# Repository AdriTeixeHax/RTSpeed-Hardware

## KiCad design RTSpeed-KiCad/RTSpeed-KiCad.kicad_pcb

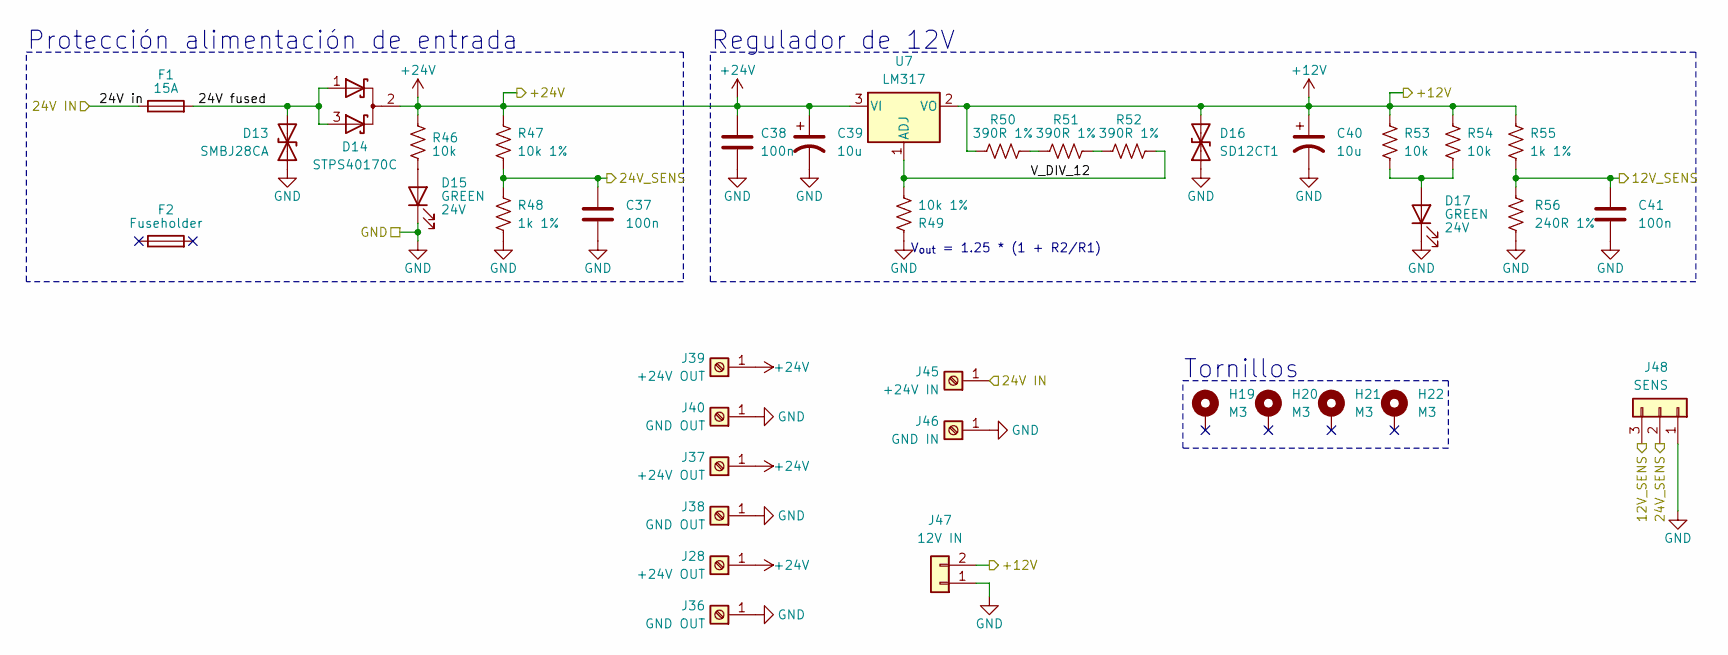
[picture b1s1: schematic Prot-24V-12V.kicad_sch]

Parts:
C37, C38, C41: 100n; C_0603_1608Metric; LCSC part C5137636
C39, C40: 10u; CP_Elec_4x5.4; LCSC part C72484
D13: SMBJ28CA; D_SMB; LCSC part C151259
D14: STPS40170C; TO-220-3_Vertical; LCSC part C222365
D15, D17: GREEN; LED_0805_2012Metric; LCSC part C965815
D16: SD12CT1; D_SOD-323_HandSoldering; LCSC part C328100
F1: 15A; Fuseholder_Automotive; LCSC part C151095
F2: Fuseholder; LCSC part C19727305
H19, H20, H21, H22: M3; MountingHole_3.2mm_M3
J28, J37, J39: +24V OUT; MountingHole_2.5mm_Pad_TopBottom
J36, J38, J40: GND OUT; MountingHole_2.5mm_Pad_TopBottom
J45: +24V IN; MountingHole_2.5mm_Pad_TopBottom
J46: GND IN; MountingHole_2.5mm_Pad_TopBottom
J47: 12V IN; JST_PH_B2B-PH-K_1x02_P2.00mm_Vertical
J48: SENS; JST_PH_B3B-PH-K_1x03_P2.00mm_Vertical
R46, R53, R54: 10k; R_0603_1608Metric; LCSC part C126901
R47, R49: 10k 1%; R_0603_1608Metric; LCSC part C126901
R48: 1k 1%; R_0603_1608Metric; LCSC part C103198
R50, R51, R52: 390R 1%; R_0603_1608Metric; LCSC part C3016257
R55: 1k 1%; R_0603_1608Metric; LCSC part C126901
R56: 240R 1%; R_0603_1608Metric; LCSC part C286579
U7: LM317; TO-220-3_Vertical; LCSC part C3014307

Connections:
+12V: C40.1, D16.2 (A2), J47.2, R50.1, R53.1, R54.1, R55.1, U7.2 (VO); also elsewhere on the board
+24V: C38.1, C39.1, D14.2 (K), J28.1, J37.1, J39.1, R46.1, R47.1, U7.3 (VI); also elsewhere on the board
/ADC/CH0: C37.1, J48.2, R47.2, R48.2; also elsewhere on the board
/ADC/CH1: C41.1, J48.3, R55.2, R56.1; also elsewhere on the board
/Protección 24V-12V/24V fused: D13.2 (A2), D14.1 (A), D14.3 (A), F1.2
/Protección 24V-12V/24V in: F1.1, J45.1; also elsewhere on the board
/Protección 24V-12V/V_DIV_12: R49.2, R52.2, U7.1 (ADJ)
GND: C37.2, C38.2, C39.2, C40.2, C41.2, D13.1 (A1), D15.1 (K), D16.1 (A1), D17.1 (K), J36.1, J38.1, J40.1, J46.1, J47.1, J48.1, R48.1, R49.1, R56.2; also elsewhere on the board
unnamed: D15.2 (A), R46.2
unnamed: D17.2 (A), R53.2, R54.2
unnamed: R50.2, R51.1
unnamed: R51.2, R52.1

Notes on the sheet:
Protección alimentación de entrada
V_{out} = 1.25 * (1 + R2/R1)
Regulador de 12V
Tornillos

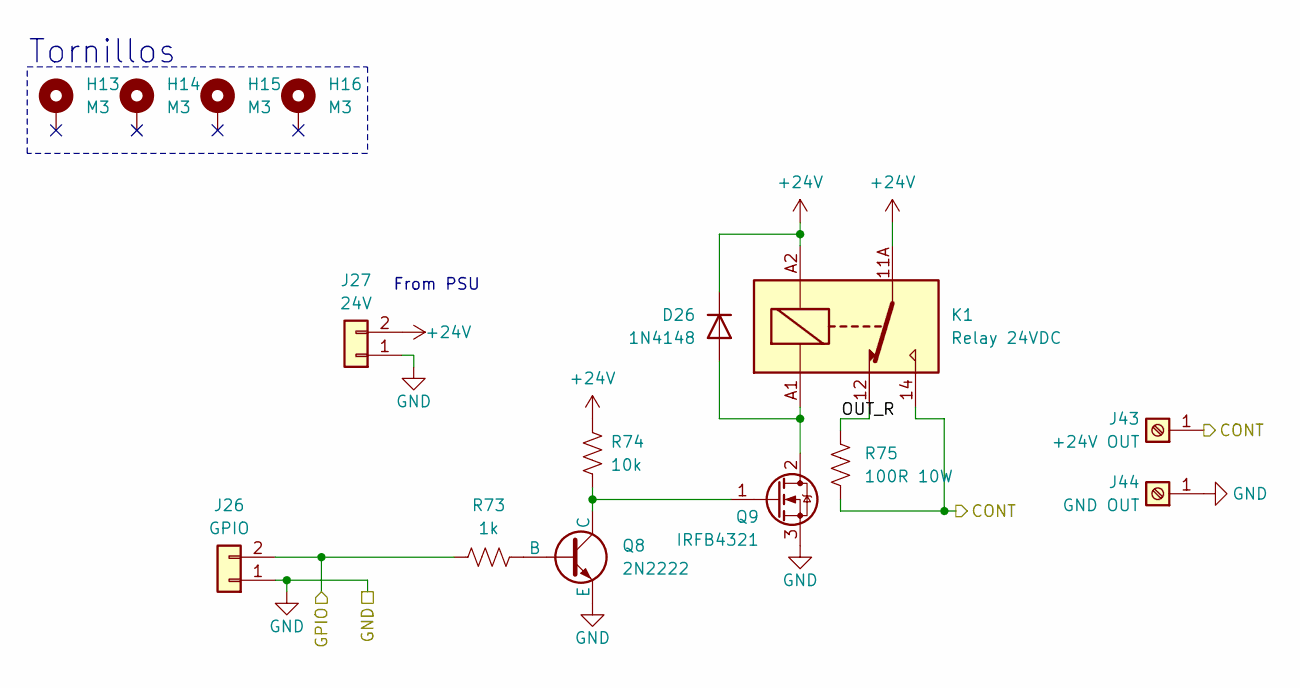
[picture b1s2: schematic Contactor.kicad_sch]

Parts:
D26: 1N4148; D_DO-35_SOD27_P7.62mm_Horizontal
H13, H14, H15, H16: M3; MountingHole_3.2mm_M3
J26: GPIO; JST_PH_B2B-PH-K_1x02_P2.00mm_Vertical
J27: 24V; Barrier_1x02
J43: +24V OUT; MountingHole_2.5mm_Pad_TopBottom
J44: GND OUT; MountingHole_2.5mm_Pad_TopBottom
K1: Relay 24VDC; Relay_SPDT_RAYEX-L90
Q8: 2N2222; TO-92_Inline
Q9: IRFB4321; TO-220-3_Vertical; LCSC part C2656
R73: 1k; R_Axial_DIN0207_L6.3mm_D2.5mm_P15.24mm_Horizontal
R74: 10k; R_Axial_DIN0207_L6.3mm_D2.5mm_P15.24mm_Horizontal
R75: 100R 10W; R_Power_22x9.5x9.5_P18mm

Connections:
+24V: D26.1 (K), J27.2, K1.11A, K1.11B, K1.A2, R74.1; also elsewhere on the board
/Contactor/OUT_R: K1.12, R75.1
/Microcontrolador/PA10: J26.2, R73.1; also elsewhere on the board
/Protección 24V-12V/24V in: J43.1, K1.14, R75.2; also elsewhere on the board
GND: J26.1, J27.1, J44.1, Q8.3 (E), Q9.3 (S); also elsewhere on the board
unnamed: D26.2 (A), K1.A1, Q9.2 (D)
unnamed: Q8.2 (B), R73.2
unnamed: Q8.1 (C), Q9.1 (G), R74.2

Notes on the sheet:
From PSU
Tornillos

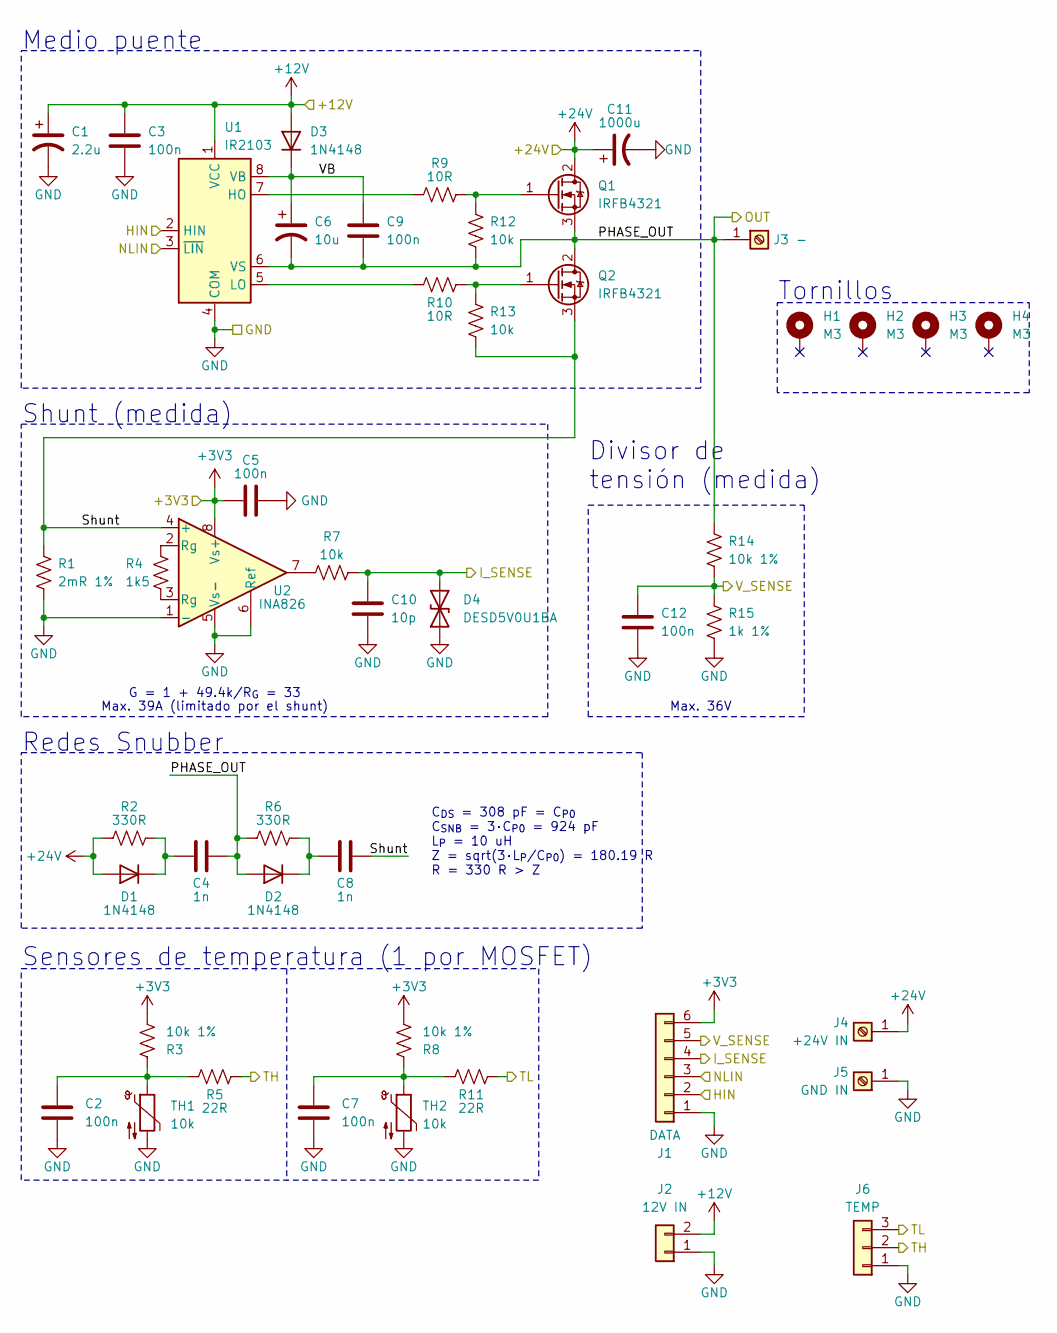
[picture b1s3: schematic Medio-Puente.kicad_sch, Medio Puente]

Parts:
C1: 2.2u; CP_Elec_4x5.4; LCSC part C72493
C2, C3, C5, C7, C9, C12: 100n; C_0603_1608Metric; LCSC part C5137636
C4, C8: 1n; C_0603_1608Metric; LCSC part C96090
C6: 10u; CP_Elec_4x5.4; LCSC part C72484
C10: 10p; C_0603_1608Metric; LCSC part C376764
C11: 1000u; CP_Radial_D12.5mm_P5.00mm; LCSC part C88743
D1, D2, D3: 1N4148; D_SOD-123; LCSC part C83528
D4: DESD5V0U1BA; D_SOD-323_HandSoldering; LCSC part C460442
H1, H2, H3, H4: M3; MountingHole_3.2mm_M3
J1: DATA; JST_PH_B6B-PH-K_1x06_P2.00mm_Vertical
J2: 12V IN; JST_PH_B2B-PH-K_1x02_P2.00mm_Vertical
J3: -; MountingHole_2.5mm_Pad_TopBottom
J4: +24V IN; MountingHole_2.5mm_Pad_TopBottom
J5: GND IN; MountingHole_2.5mm_Pad_TopBottom
J6: TEMP; JST_PH_B3B-PH-K_1x03_P2.00mm_Vertical
Q1, Q2: IRFB4321; TO-220-3_Vertical; LCSC part C2656
R1: 2mR 1%; R_2512_6332Metric; LCSC part C2994640
R2, R6: 330R; R_0603_1608Metric; LCSC part C2933198
R3, R8, R14: 10k 1%; R_0603_1608Metric; LCSC part C126901
R4: 1k5; R_0603_1608Metric; LCSC part C3016293
R5, R11: 22R; R_0603_1608Metric; LCSC part C163887
R7, R12, R13: 10k; R_0603_1608Metric; LCSC part C126901
R9, R10: 10R; R_0805_2012Metric; LCSC part C3016584
R15: 1k 1%; R_0603_1608Metric; LCSC part C103198
TH1: 10k; temp sensor; LCSC part C84036
TH2: 10k; temp sensor; LCSC part C123383
U1: IR2103; SOIC-8_3.9x4.9mm_P1.27mm; LCSC part C2957
U2: INA826; SOIC-8_3.9x4.9mm_P1.27mm; LCSC part C51631

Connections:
+3V3: C5.1, J1.6, R3.2, R8.2, U2.8 (Vs+); also elsewhere on the board
+12V: C1.1, C3.1, D3.2 (A), J2.2, U1.1 (VCC); also elsewhere on the board
+24V: C11.1, D1.2 (A), J4.1, Q1.2 (D), R2.2; also elsewhere on the board
/ADC/CH2: J6.2, R5.1; also elsewhere on the board
/ADC/CH3: J6.3, R11.1; also elsewhere on the board
/Medio-Puente-U/PHASE_OUT: C4.2, C6.2, C9.2, D2.2 (A), J3.1, Q1.3 (S), Q2.2 (D), R6.2, R12.1, R14.2, U1.6 (VS); also elsewhere on the board
/Medio-Puente-U/Shunt: C8.2, Q2.3 (S), R1.1, R13.1, U2.4 (+)
/Medio-Puente-U/VB: C6.1, C9.1, D3.1 (K), U1.8 (VB)
/Microcontrolador/PA8: J1.3, U1.3 (~LIN); also elsewhere on the board
/Microcontrolador/PA9: J1.2, U1.2 (HIN); also elsewhere on the board
/Microcontrolador/PB0: C12.1, J1.5, R14.1, R15.2; also elsewhere on the board
/Microcontrolador/PB1: C10.2, D4.2 (A2), J1.4, R7.2; also elsewhere on the board
GND: C1.2, C2.2, C3.2, C5.2, C7.2, C10.1, C11.2, C12.2, D4.1 (A1), J1.1, J2.1, J5.1, J6.1, R1.2, R15.1, TH1.2, TH2.2, U1.4 (COM), U2.1 (-), U2.5 (Vs-), U2.6 (Ref); also elsewhere on the board
unnamed: C2.1, R3.1, R5.2, TH1.1
unnamed: C7.1, R8.1, R11.2, TH2.1
unnamed: C4.1, D1.1 (K), R2.1
unnamed: C8.1, D2.1 (K), R6.1
unnamed: Q1.1 (G), R9.2, R12.2
unnamed: Q2.1 (G), R10.1, R13.2
unnamed: R4.1, U2.2 (Rg)
unnamed: R4.2, U2.3 (Rg)
unnamed: R7.1, U2.7
unnamed: R9.1, U1.7 (HO)
unnamed: R10.2, U1.5 (LO)

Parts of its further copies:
C13, C25: 2.2u; CP_Elec_4x5.4; LCSC part C72493
C14, C15, C17, C19, C21, C24, C26, C27, C29, C31, C33, C36: 100n; C_0603_1608Metric; LCSC part C5137636
C16, C20, C28, C32: 1n; C_0603_1608Metric; LCSC part C96090
C18, C30: 10u; CP_Elec_4x5.4; LCSC part C72484
C22, C34: 10p; C_0603_1608Metric; LCSC part C376764
C23, C35: 1000u; CP_Radial_D12.5mm_P5.00mm; LCSC part C88743
D5, D6, D7, D9, D10, D11: 1N4148; D_SOD-123; LCSC part C83528
D8, D12: DESD5V0U1BA; D_SOD-323_HandSoldering; LCSC part C460442
H5, H6, H7, H8, H9, H10, H11, H12: M3; MountingHole_3.2mm_M3
J7, J13: DATA; JST_PH_B6B-PH-K_1x06_P2.00mm_Vertical
J8, J14: 12V IN; JST_PH_B2B-PH-K_1x02_P2.00mm_Vertical
J9, J15: -; MountingHole_2.5mm_Pad_TopBottom
J10, J16: +24V IN; MountingHole_2.5mm_Pad_TopBottom
J11, J17: GND IN; MountingHole_2.5mm_Pad_TopBottom
J12, J18: TEMP; JST_PH_B3B-PH-K_1x03_P2.00mm_Vertical
Q3, Q4, Q5, Q6: IRFB4321; TO-220-3_Vertical; LCSC part C2656
R16, R31: 2mR 1%; R_2512_6332Metric; LCSC part C2994640
R17, R21, R32, R36: 330R; R_0603_1608Metric; LCSC part C2933198
R18, R23, R29, R33, R38, R44: 10k 1%; R_0603_1608Metric; LCSC part C126901
R19, R34: 1k5; R_0603_1608Metric; LCSC part C3016293
R20, R26, R35, R41: 22R; R_0603_1608Metric; LCSC part C163887
R22, R27, R28, R37, R42, R43: 10k; R_0603_1608Metric; LCSC part C126901
R24, R25, R39, R40: 10R; R_0805_2012Metric; LCSC part C3016584
R30, R45: 1k 1%; R_0603_1608Metric; LCSC part C103198
TH3, TH5: 10k; temp sensor; LCSC part C84036
TH4, TH6: 10k; temp sensor; LCSC part C123383
U3, U5: IR2103; SOIC-8_3.9x4.9mm_P1.27mm; LCSC part C2957
U4, U6: INA826; SOIC-8_3.9x4.9mm_P1.27mm; LCSC part C51631

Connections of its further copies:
+3V3: C17.1, C29.1, J7.6, J13.6, R18.2, R23.2, R33.2, R38.2, U4.8 (Vs+), U6.8 (Vs+); also elsewhere on the board
+12V: C13.1, C15.1, C25.1, C27.1, D7.2 (A), D11.2 (A), J8.2, J14.2, U3.1 (VCC), U5.1 (VCC); also elsewhere on the board
+24V: C23.1, C35.1, D5.2 (A), D9.2 (A), J10.1, J16.1, Q3.2 (D), Q5.2 (D), R17.2, R32.2; also elsewhere on the board
/ADC/CH4: J12.2, R20.1; also elsewhere on the board
/ADC/CH5: J12.3, R26.1; also elsewhere on the board
/ADC/CH6: J18.2, R35.1; also elsewhere on the board
/ADC/CH7: J18.3, R41.1; also elsewhere on the board
/Medio-Puente-V/PHASE_OUT: C16.2, C18.2, C21.2, D6.2 (A), J9.1, Q3.3 (S), Q4.2 (D), R21.2, R27.1, R29.2, U3.6 (VS); also elsewhere on the board
/Medio-Puente-V/Shunt: C20.2, Q4.3 (S), R16.1, R28.1, U4.4 (+)
/Medio-Puente-V/VB: C18.1, C21.1, D7.1 (K), U3.8 (VB)
/Medio-Puente-W/PHASE_OUT: C28.2, C30.2, C33.2, D10.2 (A), J15.1, Q5.3 (S), Q6.2 (D), R36.2, R42.1, R44.2, U5.6 (VS); also elsewhere on the board
/Medio-Puente-W/Shunt: C32.2, Q6.3 (S), R31.1, R43.1, U6.4 (+)
/Medio-Puente-W/VB: C30.1, C33.1, D11.1 (K), U5.8 (VB)
/Microcontrolador/PA0: C36.1, J13.5, R44.1, R45.2; also elsewhere on the board
/Microcontrolador/PA1: C34.2, D12.2 (A2), J13.4, R37.2; also elsewhere on the board
/Microcontrolador/PA2: J13.3, U5.3 (~LIN); also elsewhere on the board
/Microcontrolador/PA3: J13.2, U5.2 (HIN); also elsewhere on the board
/Microcontrolador/PA4: C24.1, J7.5, R29.1, R30.2; also elsewhere on the board
/Microcontrolador/PA5: C22.2, D8.2 (A2), J7.4, R22.2; also elsewhere on the board
/Microcontrolador/PA6: J7.3, U3.3 (~LIN); also elsewhere on the board
/Microcontrolador/PA7: J7.2, U3.2 (HIN); also elsewhere on the board
GND: C13.2, C14.2, C15.2, C17.2, C19.2, C22.1, C23.2, C24.2, C25.2, C26.2, C27.2, C29.2, C31.2, C34.1, C35.2, C36.2, D8.1 (A1), D12.1 (A1), J7.1, J8.1, J11.1, J12.1, J13.1, J14.1, J17.1, J18.1, R16.2, R30.1, R31.2, R45.1, TH3.2, TH4.2, TH5.2, TH6.2, U3.4 (COM), U4.1 (-), U4.5 (Vs-), U4.6 (Ref), U5.4 (COM), U6.1 (-), U6.5 (Vs-), U6.6 (Ref); also elsewhere on the board
unnamed: C14.1, R18.1, R20.2, TH3.1
unnamed: C19.1, R23.1, R26.2, TH4.1
unnamed: C26.1, R33.1, R35.2, TH5.1
unnamed: C31.1, R38.1, R41.2, TH6.1
unnamed: C16.1, D5.1 (K), R17.1
unnamed: C20.1, D6.1 (K), R21.1
unnamed: C28.1, D9.1 (K), R32.1
unnamed: C32.1, D10.1 (K), R36.1
unnamed: Q3.1 (G), R24.2, R27.2
unnamed: Q4.1 (G), R25.1, R28.2
unnamed: Q5.1 (G), R39.2, R42.2
unnamed: Q6.1 (G), R40.1, R43.2
unnamed: R19.1, U4.2 (Rg)
unnamed: R19.2, U4.3 (Rg)
unnamed: R22.1, U4.7
unnamed: R34.1, U6.2 (Rg)
unnamed: R34.2, U6.3 (Rg)
unnamed: R37.1, U6.7
unnamed: R24.1, U3.7 (HO)
unnamed: R25.2, U3.5 (LO)
unnamed: R39.1, U5.7 (HO)
unnamed: R40.2, U5.5 (LO)

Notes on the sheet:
Max. 39A (limitado por el shunt)
Medio puente
C_{DS} = 308 pF = C_{P0} C_{SNB} = 3·C_{P0} = 924 pF L_{P} = 10 uH Z = sqrt(3·L_{P}/C_{P0}) = 180.19 R R = 330 R > Z
Divisor de tensión (medida)
Max. 36V
Redes Snubber
Shunt (medida)
Tornillos
G = 1 + 49.4k/R_{G} = 33
Sensores de temperatura (1 por MOSFET)

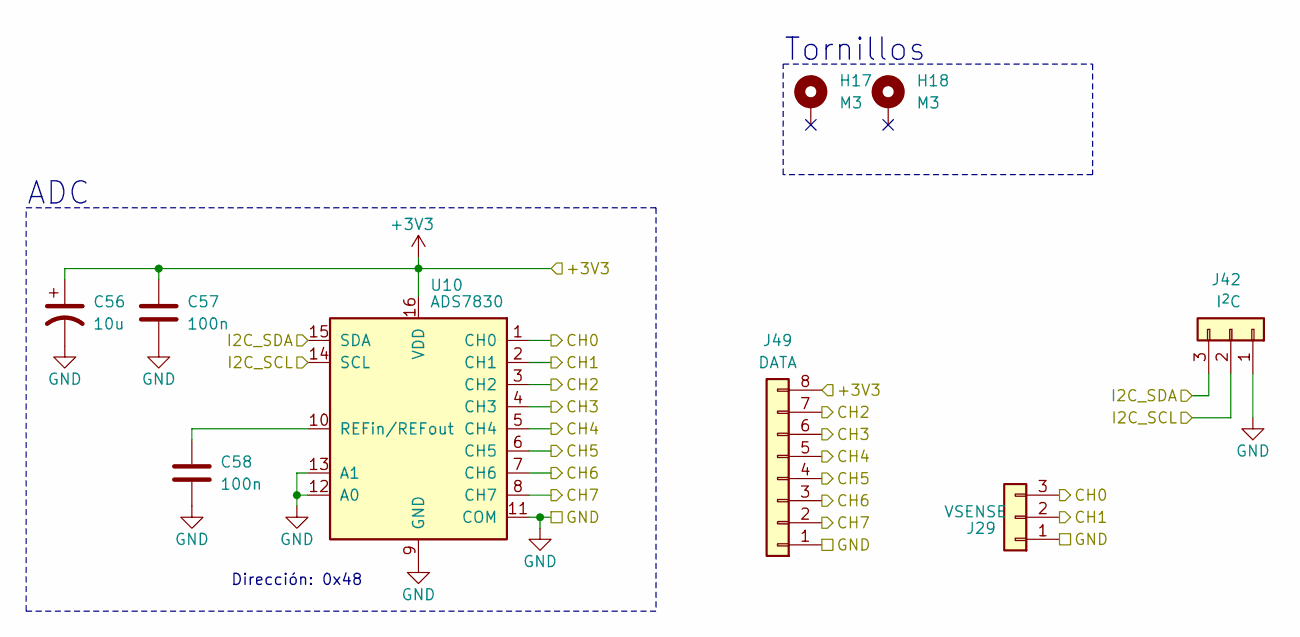
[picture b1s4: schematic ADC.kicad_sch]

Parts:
C56: 10u; CP_Elec_4x5.4; LCSC part C72484
C57, C58: 100n; C_0603_1608Metric; LCSC part C5137636
H17, H18: M3; MountingHole_3.2mm_M3
J29: VSENSE; JST_PH_B3B-PH-K_1x03_P2.00mm_Vertical
J42: I^{2}C; JST_PH_B3B-PH-K_1x03_P2.00mm_Vertical
J49: DATA; JST_PH_B8B-PH-K_1x08_P2.00mm_Vertical
U10: ADS7830; TSSOP-16_4.4x5mm_P0.65mm; LCSC part C161747

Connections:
+3V3: C56.1, C57.1, J49.8, U10.16 (VDD); also elsewhere on the board
/ADC/CH0: J29.3, U10.1 (CH0); also elsewhere on the board
/ADC/CH1: J29.2, U10.2 (CH1); also elsewhere on the board
/ADC/CH2: J49.7, U10.3 (CH2); also elsewhere on the board
/ADC/CH3: J49.6, U10.4 (CH3); also elsewhere on the board
/ADC/CH4: J49.5, U10.5 (CH4); also elsewhere on the board
/ADC/CH5: J49.4, U10.6 (CH5); also elsewhere on the board
/ADC/CH6: J49.3, U10.7 (CH6); also elsewhere on the board
/ADC/CH7: J49.2, U10.8 (CH7); also elsewhere on the board
/Microcontrolador/I2C_SCL: J42.2, U10.14 (SCL); also elsewhere on the board
/Microcontrolador/I2C_SDA: J42.3, U10.15 (SDA); also elsewhere on the board
GND: C56.2, C57.2, C58.2, J29.1, J42.1, J49.1, U10.9 (GND), U10.11 (COM), U10.12 (A0), U10.13 (A1); also elsewhere on the board
unnamed: C58.1, U10.10 (REFin/REFout)

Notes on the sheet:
ADC
Dirección: 0x48
Tornillos

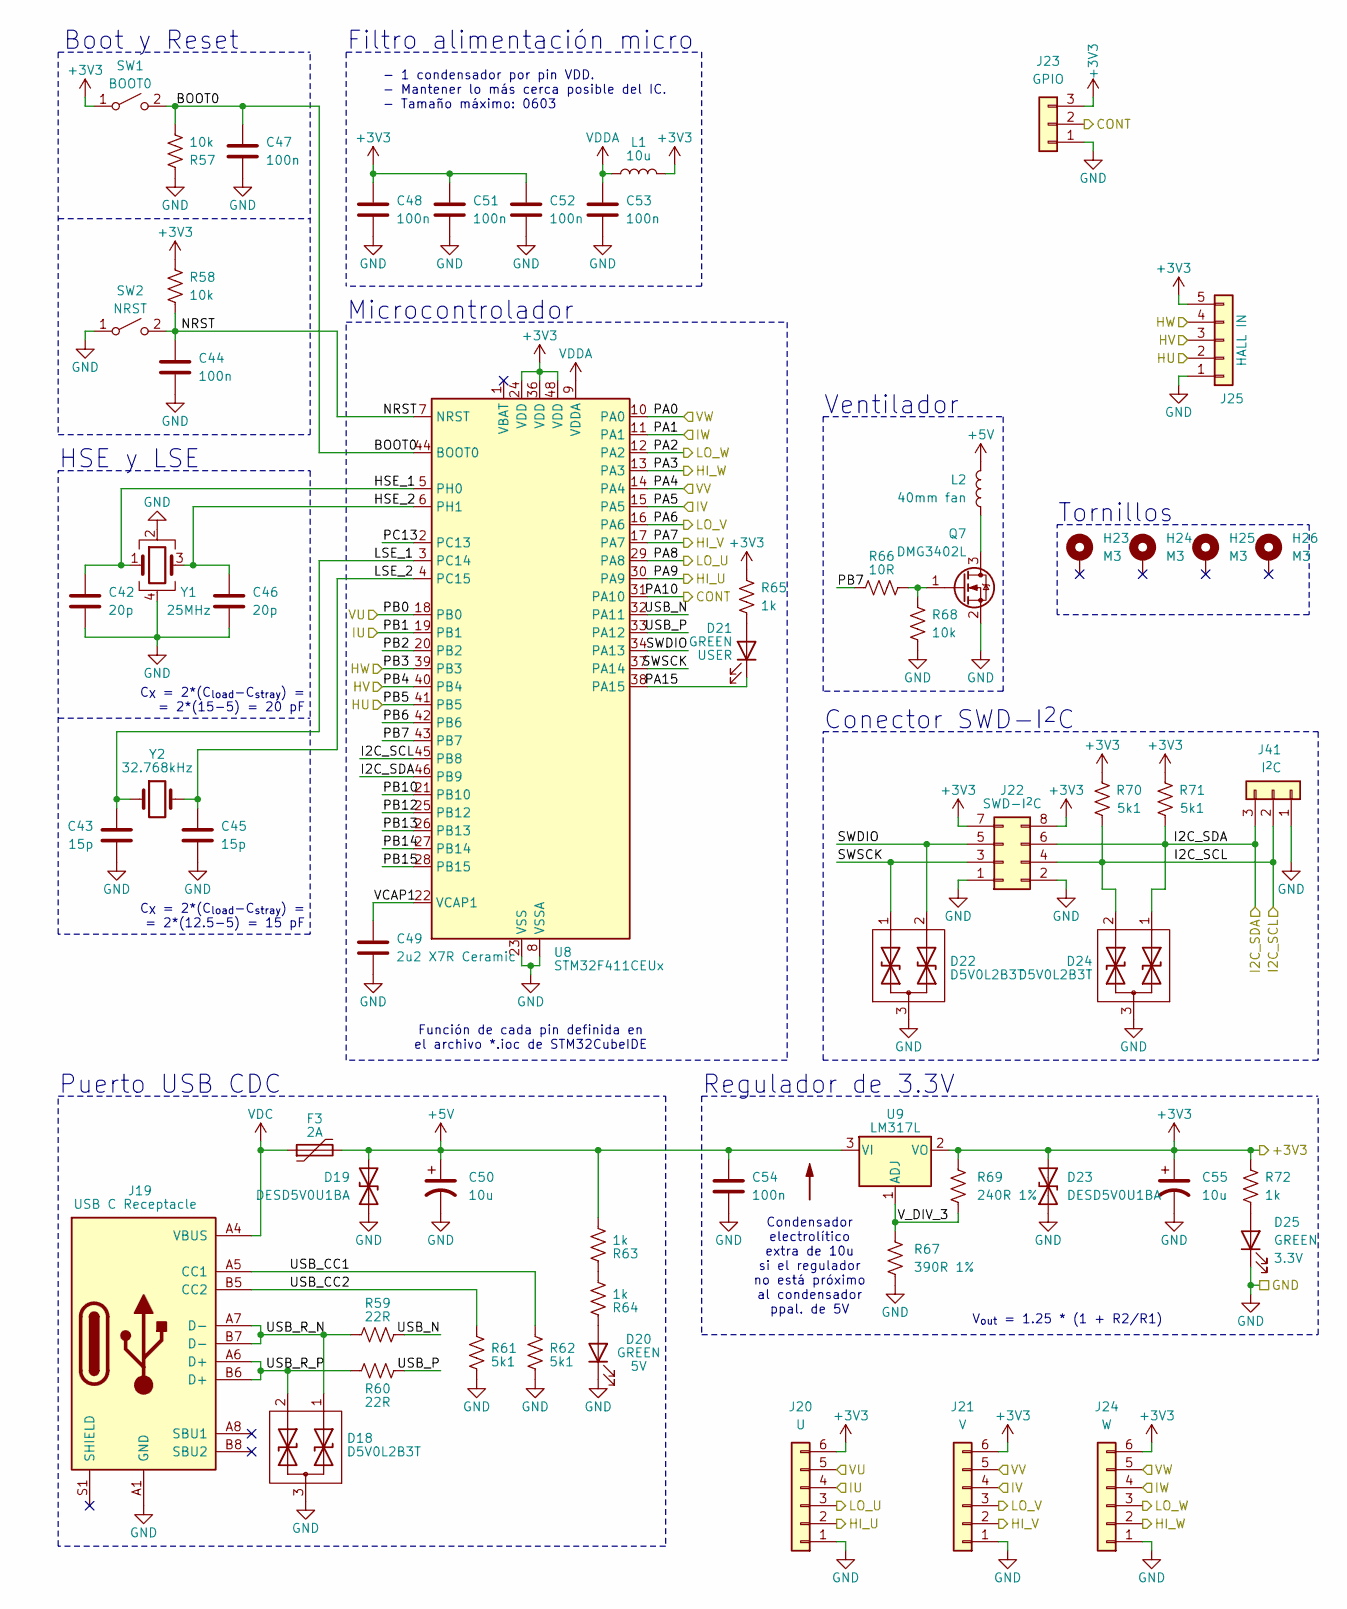
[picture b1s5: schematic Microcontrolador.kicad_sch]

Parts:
C42, C46: 20p; C_0603_1608Metric; LCSC part C376774
C43, C45: 15p; C_0603_1608Metric; LCSC part C1644
C44, C47, C48, C51, C52, C53, C54: 100n; C_0603_1608Metric; LCSC part C5137636
C49: 2u2 X7R Ceramic; C_0603_1608Metric; LCSC part C7393903
C50: 10u; CP_Elec_4x5.4; LCSC Part C72485
C55: 10u; CP_Elec_4x5.4; LCSC part C72484
D18, D22, D24: D5V0L2B3T; SOT-523; LCSC part C526508
D19, D23: DESD5V0U1BA; D_SOD-323_HandSoldering; LCSC part C460442
D20, D21, D25: GREEN; LED_0805_2012Metric; LCSC part C965815
F3: 2A; Fuse_1812_4532Metric; LCSC part C2649915
H23, H24, H25, H26: M3; MountingHole_3.2mm_M3
J19: USB C Receptacle; USB_C_Receptacle_XKB_U262-16XN-4BVC11; LCSC part C2765186
J20: U; JST_PH_B6B-PH-K_1x06_P2.00mm_Vertical
J21: V; JST_PH_B6B-PH-K_1x06_P2.00mm_Vertical
J22: SWD-I^{2}C; PinHeader_2x04_P2.54mm_Vertical; LCSC part C492432
J23: GPIO; JST_PH_B3B-PH-K_1x03_P2.00mm_Vertical
J24: W; JST_PH_B6B-PH-K_1x06_P2.00mm_Vertical
J25: HALL IN; JST_PH_B5B-PH-K_1x05_P2.00mm_Vertical; LCSC part C157923
J41: I^{2}C; JST_PH_B3B-PH-K_1x03_P2.00mm_Vertical
L1: 10u; L_0805_2012Metric; LCSC part C99366
L2: 40mm fan; JST_PH_B2B-PH-K_1x02_P2.00mm_Vertical; LCSC part C131337
Q7: DMG3402L; SOT-23; LCSC part C3647055
R57, R58, R68: 10k; R_0603_1608Metric; LCSC part C126901
R59, R60: 22R; R_0603_1608Metric; LCSC part C163887
R61, R62: 5k1; R_0603_1608Metric; LCSC part C2907114
R63, R64, R65, R72: 1k; R_0603_1608Metric; LCSC part C126901
R66: 10R; R_0805_2012Metric; LCSC part C3016584
R67: 390R 1%; R_0603_1608Metric; LCSC part C3016257
R69: 240R 1%; R_0603_1608Metric; LCSC part C286579
R70, R71: 5k1; R_0603_1608Metric; LCSC part C126901
SW1: BOOT0; SPDT; LCSC part C455282
SW2: NRST; SPDT; LCSC part C455282
U8: STM32F411CEUx; QFN-48-1EP_7x7mm_P0.5mm_EP5.6x5.6mm; LCSC part C60420
U9: LM317L; SOT-89-3; LCSC part C112537
Y1: 25MHz; Oscillator_SMD_Abracon_ASE-4Pin_3.2x2.5mm; LCSC part C2901686
Y2: 32.768kHz; Crystal_SMD_3215-2Pin_3.2x1.5mm; LCSC part C97606

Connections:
+3V3: C48.1, C51.1, C52.1, C55.1, D23.2 (A2), J20.6, J21.6, J22.7, J22.8, J23.3, J24.6, J25.5, L1.2, R58.1, R65.1, R69.1, R70.2, R71.2, R72.1, SW1.1 (A), U8.24 (VDD), U8.36 (VDD), U8.48 (VDD), U9.2 (VO); also elsewhere on the board
+5V: C50.1, C54.1, D19.2 (A2), F3.2, L2.1, R63.1, U9.3 (VI)
/Microcontrolador/BOOT0: C47.2, R57.2, SW1.2 (B), U8.44 (BOOT0)
/Microcontrolador/HSE_1: C42.1, U8.5 (PH0), Y1.1
/Microcontrolador/HSE_2: C46.1, U8.6 (PH1), Y1.3
/Microcontrolador/I2C_SCL: D24.2, J22.4, J41.2, R70.1, U8.45 (PB8); also elsewhere on the board
/Microcontrolador/I2C_SDA: D24.1, J22.6, J41.3, R71.1, U8.46 (PB9); also elsewhere on the board
/Microcontrolador/LSE_1: C43.1, U8.3 (PC14), Y2.1
/Microcontrolador/LSE_2: C45.1, U8.4 (PC15), Y2.2
/Microcontrolador/NRST: C44.2, R58.2, SW2.2 (B), U8.7 (NRST)
/Microcontrolador/PA0: J24.5, U8.10 (PA0); also elsewhere on the board
/Microcontrolador/PA1: J24.4, U8.11 (PA1); also elsewhere on the board
/Microcontrolador/PA2: J24.3, U8.12 (PA2); also elsewhere on the board
/Microcontrolador/PA3: J24.2, U8.13 (PA3); also elsewhere on the board
/Microcontrolador/PA4: J21.5, U8.14 (PA4); also elsewhere on the board
/Microcontrolador/PA5: J21.4, U8.15 (PA5); also elsewhere on the board
/Microcontrolador/PA6: J21.3, U8.16 (PA6); also elsewhere on the board
/Microcontrolador/PA7: J21.2, U8.17 (PA7); also elsewhere on the board
/Microcontrolador/PA8: J20.3, U8.29 (PA8); also elsewhere on the board
/Microcontrolador/PA9: J20.2, U8.30 (PA9); also elsewhere on the board
/Microcontrolador/PA10: J23.2, U8.31 (PA10); also elsewhere on the board
/Microcontrolador/PA15: D21.1 (K), U8.38 (PA15)
/Microcontrolador/PB0: J20.5, U8.18 (PB0); also elsewhere on the board
/Microcontrolador/PB1: J20.4, U8.19 (PB1); also elsewhere on the board
/Microcontrolador/PB2: U8.20 (PB2)
/Microcontrolador/PB3: J25.4, U8.39 (PB3); also elsewhere on the board
/Microcontrolador/PB4: J25.3, U8.40 (PB4); also elsewhere on the board
/Microcontrolador/PB5: J25.2, U8.41 (PB5); also elsewhere on the board
/Microcontrolador/PB6: U8.42 (PB6)
/Microcontrolador/PB7: R66.1, U8.43 (PB7)
/Microcontrolador/PB10: U8.21 (PB10)
/Microcontrolador/PB12: U8.25 (PB12)
/Microcontrolador/PB13: U8.26 (PB13)
/Microcontrolador/PB14: U8.27 (PB14)
/Microcontrolador/PB15: U8.28 (PB15)
/Microcontrolador/PC13: U8.2 (PC13)
/Microcontrolador/SWDIO: D22.2, J22.5, U8.34 (PA13)
/Microcontrolador/SWSCK: D22.1, J22.3, U8.37 (PA14)
/Microcontrolador/USB_CC1: J19.A5 (CC1), R62.2
/Microcontrolador/USB_CC2: J19.B5 (CC2), R61.1
/Microcontrolador/USB_N: R59.2, U8.32 (PA11)
/Microcontrolador/USB_P: R60.2, U8.33 (PA12)
/Microcontrolador/USB_R_N: D18.1, J19.A7 (D-), J19.B7 (D-), R59.1
/Microcontrolador/USB_R_P: D18.2, J19.A6 (D+), J19.B6 (D+), R60.1
/Microcontrolador/VCAP1: C49.1, U8.22 (VCAP1)
/Microcontrolador/V_DIV_3: R67.1, R69.2, U9.1 (ADJ)
GND: C42.2, C43.2, C44.1, C45.2, C46.2, C47.1, C48.2, C49.2, C50.2, C51.2, C52.2, C53.2, C54.2, C55.2, D18.3, D19.1 (A1), D20.1 (K), D22.3, D23.1 (A1), D24.3, D25.1 (K), J19.A1 (GND), J19.A12 (GND), J19.B1 (GND), J19.B12 (GND), J20.1, J21.1, J22.1, J22.2, J23.1, J24.1, J25.1, J41.1, Q7.2 (S), R57.1, R61.2, R62.1, R67.2, R68.1, SW2.1 (A), U8.8 (VSSA), U8.23 (VSS), U8.35 (VSS), U8.47 (VSS), U8.49 (VSS), Y1.2, Y1.4; also elsewhere on the board
unnamed: D20.2 (A), R64.2
unnamed: D21.2 (A), R65.2
unnamed: D25.2 (A), R72.2
unnamed: L2.2, Q7.3 (D)
unnamed: Q7.1 (G), R66.2, R68.2
unnamed: R63.2, R64.1
VDC: F3.1, J19.A4 (VBUS), J19.A9 (VBUS), J19.B4 (VBUS), J19.B9 (VBUS)
VDDA: C53.1, L1.1, U8.9 (VDDA)

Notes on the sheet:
Microcontrolador
Función de cada pin definida en el archivo *.ioc de STM32CubeIDE
- 1 condensador por pin VDD. - Mantener lo más cerca posible del IC. - Tamaño máximo: 0603
Ventilador
C_{X} = 2*(C_{load}-C_{stray}) = = 2*(12.5-5) = 15 pF
Condensador electrolítico extra de 10u si el regulador no está próximo al condensador ppal. de 5V
Conector SWD-I^{2}C
C_{X} = 2*(C_{load}-C_{stray}) = = 2*(15-5) = 20 pF
HSE y LSE
Puerto USB CDC
Regulador de 3.3V
Boot y Reset
Tornillos
Filtro alimentación micro
V_{out} = 1.25 * (1 + R2/R1)

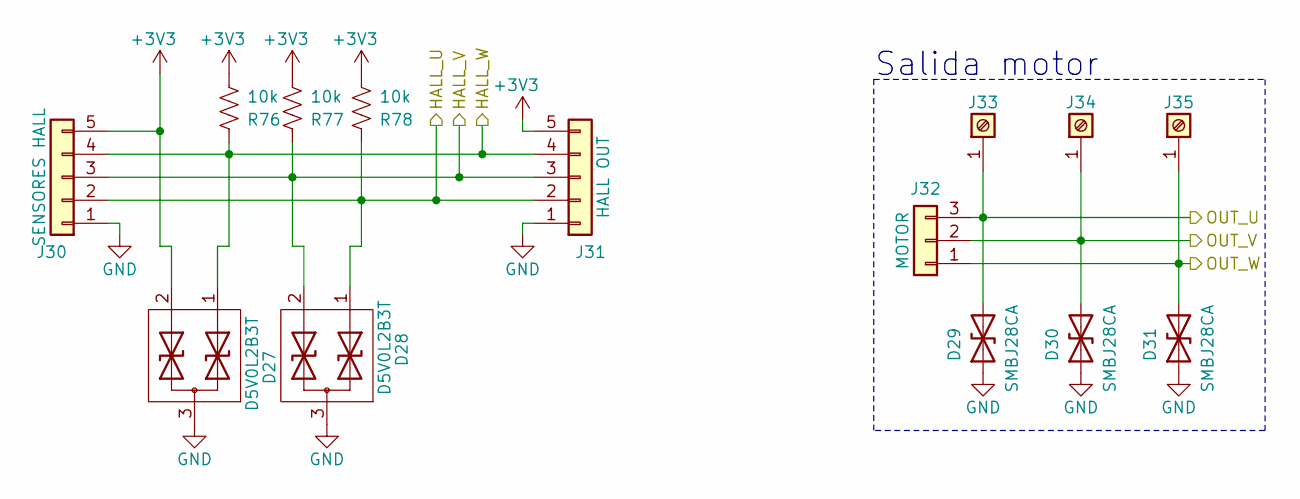
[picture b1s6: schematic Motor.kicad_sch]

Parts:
D27, D28: D5V0L2B3T; SOT-523; LCSC part C526508
D29, D30, D31: SMBJ28CA; D_SMB; LCSC part C151259
J30: SENSORES HALL; JST_PH_S5B-PH-K_1x05_P2.00mm_Horizontal; LCSC part C157923
J31: HALL OUT; JST_PH_B5B-PH-K_1x05_P2.00mm_Vertical; LCSC part C157923
J32: MOTOR; Barrier_1x03; LCSC part C395959
J33, J34, J35: -; MountingHole_2.5mm_Pad_TopBottom
R76, R77, R78: 10k; R_0603_1608Metric; LCSC part C126901

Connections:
+3V3: D27.2, J30.5, J31.5, R76.2, R77.2, R78.2; also elsewhere on the board
/Medio-Puente-U/PHASE_OUT: D29.2 (A2), J32.3, J33.1; also elsewhere on the board
/Medio-Puente-V/PHASE_OUT: D30.2 (A2), J32.2, J34.1; also elsewhere on the board
/Medio-Puente-W/PHASE_OUT: D31.2 (A2), J32.1, J35.1; also elsewhere on the board
/Microcontrolador/PB3: D27.1, J30.4, J31.4, R76.1; also elsewhere on the board
/Microcontrolador/PB4: D28.2, J30.3, J31.3, R77.1; also elsewhere on the board
/Microcontrolador/PB5: D28.1, J30.2, J31.2, R78.1; also elsewhere on the board
GND: D27.3, D28.3, D29.1 (A1), D30.1 (A1), D31.1 (A1), J30.1, J31.1; also elsewhere on the board

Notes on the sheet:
Salida motor

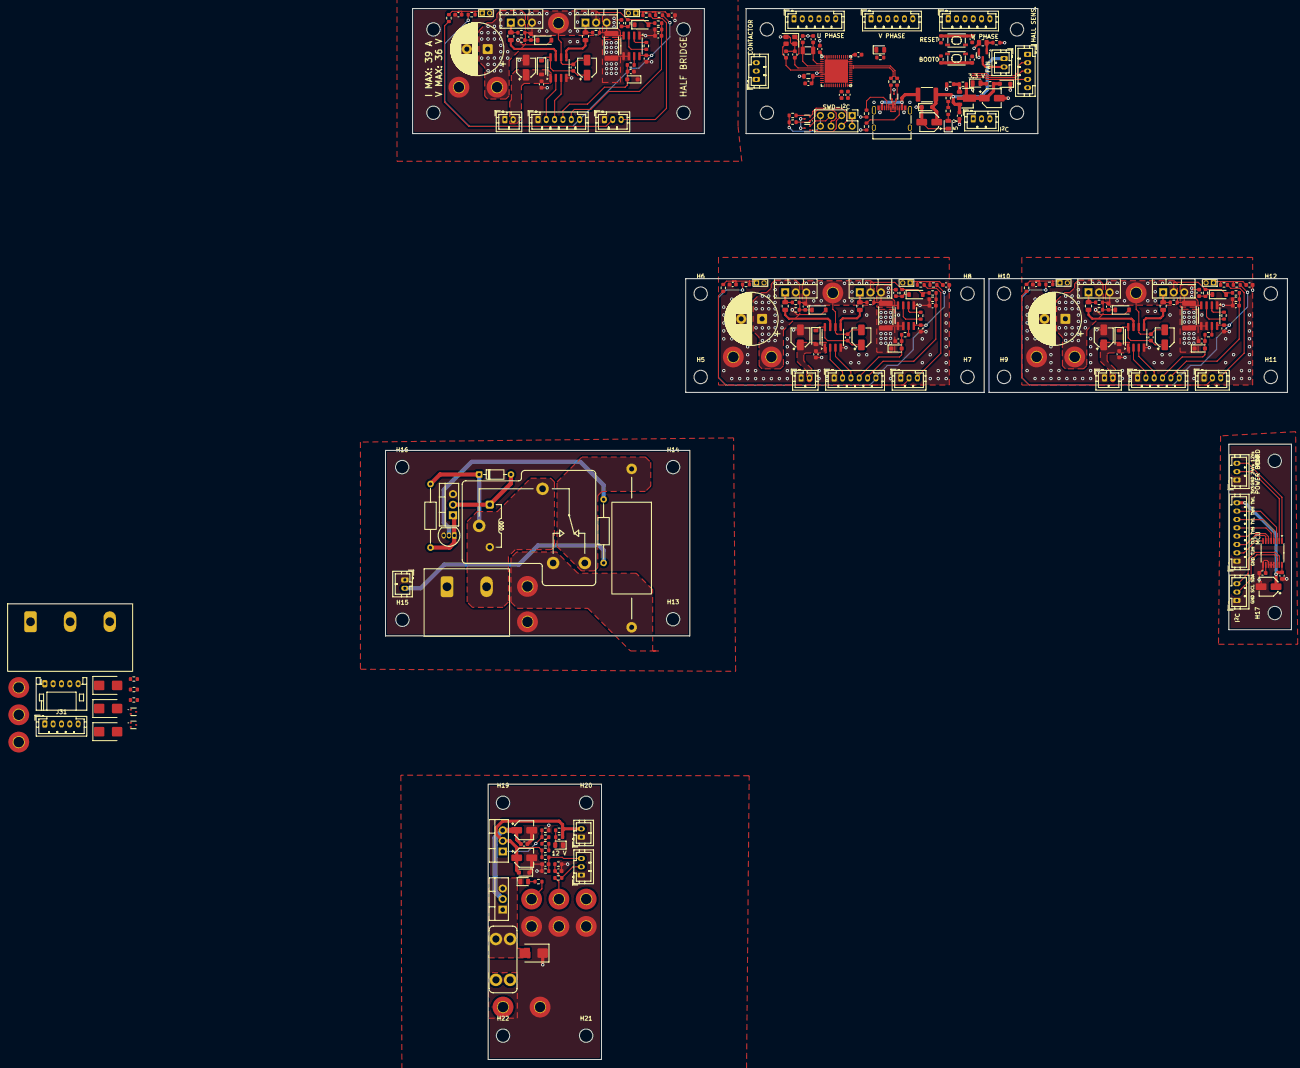
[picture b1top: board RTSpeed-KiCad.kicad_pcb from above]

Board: 2 copper layers, 217.3 x 252.1 mm, 276 parts (0 on the bottom side), 111 nets.

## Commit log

2025-10-05 Added automatic contactor PCB
2025-10-11 Contactor control pcb
2025-10-25 PCB redesign (not final)
